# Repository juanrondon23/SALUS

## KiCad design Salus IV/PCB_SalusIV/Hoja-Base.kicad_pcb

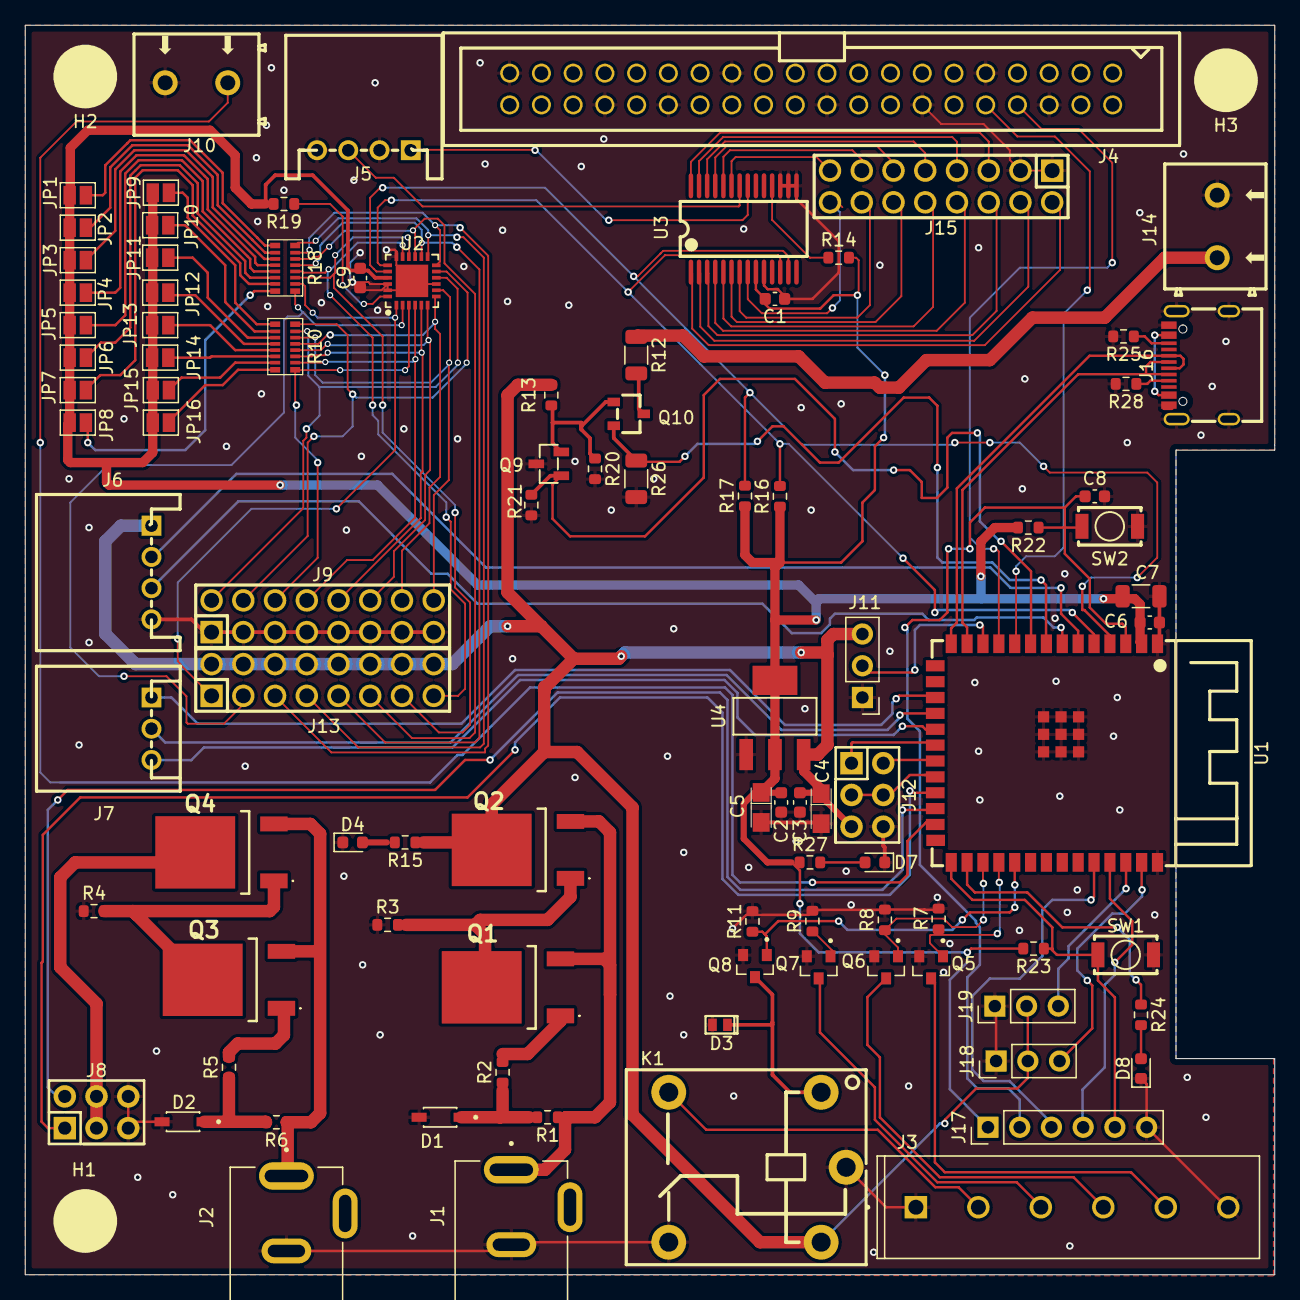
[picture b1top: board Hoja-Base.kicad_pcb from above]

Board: 2 copper layers, 100.0 x 100.0 mm, 98 parts (0 on the bottom side), 107 nets.

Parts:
C1, C2, C3, C6, C8, C9: 100nF; C_0603_1608Metric
C4, C5: 22uF; CASE-A_3216
C7: 22uF; C_1206_3216Metric
D1: BZT52C3V3; SOD3715X135N
D2: BZT52C5V1; SOD3715X135N
D3: TPTVS0971P; DFN1610-2L_L1.6-W1.0-P1.10-RD
D4: LED_Encendido; LED_0603_1608Metric
D7: LED_ESP32_RED; LED_0603_1608Metric
D8: LED_ESP32_YELLOW; LED_0603_1608Metric
H1, H2, H3: MountingHole; MountingHole_3.2mm_M3
J1, J2: DC-005-5A-2.0; XKB_DC-005-5A-2.0
J3: 282836-6; TE_282836-6
J4: IDC-TH_40P-P2.54_C9138
J5, J6: CONN-TH_S4B-XH-A-LF-SN
J7: CONN-TH_S3B-XH-A-LF-SN
J8, J12: HDR-TH_6P-P2.54-V-M-R2-C3-S2.54-1
J9, J13, J15: HDR-TH_16P-P2.54-V-M-R2-C8-S2.54
J10, J14: CONN-TH_2P-P5.00_CPC3703CTR
J11: RC; PinHeader_1x03_P2.54mm_Vertical
J16: USB-C-SMD_G-SWITCH_GT-USB-7010ASV
J17: Pruebas; PinHeader_1x06_P2.54mm_Vertical
J18: GPIO2-Libre; PinHeader_1x03_P2.54mm_Vertical
J19: GPIO1-Libre; PinHeader_1x03_P2.54mm_Vertical
JP1, JP2, JP3, JP4, JP5, JP6, JP7, JP8, JP9, JP10, JP11, JP12, JP13, JP14, JP15, JP16: Jumper_Soldado; SolderJumper-2_P1.3mm_Open_Pad1.0x1.5mm
K1: Relé-Arranque; RELAY-TH_SRD-XXVDC-XL-C
Q1, Q2, Q3, Q4: IRFR5305TRPBF
Q5, Q6, Q7, Q8: IRLML6344TRPBF; TRANS_IRLML6344TRPBF
Q9: SI2301CDS
Q10: RQ5P0
R1, R6, R13: 1K; R_0603_1608Metric
R2, R5, R7, R8, R9, R11, R20, R21: 47K; R_0603_1608Metric
R3, R4: 6.8K; R_0603_1608Metric
R10, R18: 4.7kΩ; RES-ARRAY-SMD_1606-16P-L4.0-W1.6-BL
R12: 47K; R_1206_3216Metric
R14, R22, R23: 10K; R_0603_1608Metric
R15: 390; R_0603_1608Metric
R16, R17, R19: 4.7K; R_0603_1608Metric
R24, R27: 180; R_0603_1608Metric
R25, R28: 5.1K; R_0603_1608Metric
R26: 1.5K; R_1206_3216Metric
SW1, SW2: Boton_Simple
U1: ESP32-S3-WROOM-1-N16; WIRELM-SMD_ESP32-S3-WROOM-1
U2: TCA; VQFN-24_L4.0-W4.0-P0.50-BL-EP2.5
U3: MCP; SSOP-28_L10.2-W5.3-P0.65-LS7.8-BL
U4: AMS; AMS1117

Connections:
7V: J8.3, J8.4, Q4.2 (D)
60V: J14.1, R12.1
+3.3V: C1.1, C2.1, C5.1, C6.1, C7.1, C9.1, J17.1, JP1.1 (A), JP2.1 (A), JP3.1 (A), JP4.1 (A), JP5.1 (A), JP6.1 (A), JP7.1 (A), JP8.1 (A), JP9.1 (A), JP10.1 (A), JP11.1 (A), JP12.1 (A), JP13.1 (A), JP14.1 (A), JP15.1 (A), JP16.1 (A), R14.2, R16.1, R17.1, R19.2, R22.2, R23.2, R27.1, U1.2 (3V3), U2.21 (VCC), U3.9 (VDD), U4.2 (VOUT), U4.4 (VOUT)
+5V: C3.1, C4.1, J6.1, J11.3, J12.5, J13.2, J13.4, J13.6, J13.8, J13.10, J13.12, J13.14, J13.16, J18.2, J19.2, K1.4, Q2.2 (D), R13.1, R15.1, U4.3 (VIN)
ACELERADOR: J10.1, U1.25 (IO48)
ADC_ES: Q10.2 (S), R26.1, U1.8 (IO15)
Arranque: Q8.1, R11.1, U1.31 (IO38)
BOOT: J17.5, R23.1, SW1.1, U1.27 (IO0)
CARRERA 1: J5.1, U3.21 (GPA0)
CARRERA 2: J5.3, U3.22 (GPA1)
Cambio: Q6.1, R8.1, U1.29 (IO36)
Control_Bat: Q9.1 (G), R21.1, U1.9 (IO16)
ENABLE: J12.3, J12.4, U1.22 (IO14)
Expansor 3: J15.15, U3.23 (GPA2)
Expansor 4: J15.13, U3.24 (GPA3)
Expansor 5: J15.11, U3.25 (GPA4)
Expansor 6: J15.9, U3.26 (GPA5)
Expansor 7: J15.7, U3.27 (GPA6)
Expansor 8: J15.5, U3.28 (GPA7)
Expansor 9: J15.16, U3.8 (GPB7)
Expansor 10: J15.14, U3.7 (GPB6)
Expansor 11: J15.12, U3.6 (GPB5)
Expansor 12: J15.10, U3.5 (GPB4)
Expansor 13: J15.8, U3.4 (GPB3)
Expansor 14: J15.6, U3.3 (GPB2)
Expansor 15: J15.4, U3.2 (GPB1)
Expansor 16: J15.2, U3.1 (GPB0)
GND: C1.2, C2.2, C3.2, C4.2, C5.2, C6.2, C7.2, C8.2, C9.2, D1.2 (A), D2.2 (A), D3.2 (A2), D4.1 (K), D7.1 (K), D8.1 (K), J1.2, J2.2, J3.1, J3.6, J4.6, J4.9, J4.14, J4.20, J4.25, J4.30, J4.34, J4.39, J5.2, J5.4, J6.4, J8.5, J8.6, J9.1, J9.3, J9.5, J9.7, J9.9, J9.11, J9.13, J9.15, J10.2, J11.1, J12.6, J14.2, J15.1, J15.3, J16.1 (SHELL), J16.2 (SHELL), J16.3 (SHELL), J16.4 (SHELL), J16.A1B12 (GND), J16.B1A12 (GND), J17.6, J18.1, J19.1, K1.3, K1.5, Q5.2, Q6.2, Q7.2, Q8.2, Q9.3 (D), R3.1, R4.1, R7.2, R8.2, R9.2, R11.2, R20.2, R21.2, R25.2, R26.2, R28.2, SW1.2, SW2.2, U1.1 (GND), U1.40 (GND), U1.41 (GND), U2.9 (GND), U2.18 (A2), U2.22 (A0), U2.23 (A1), U2.25 (EP), U3.10 (VSS), U3.15 (A0), U3.16 (A1), U3.17 (A2), U4.1 (GND)
GPIO1: J18.3, U1.39 (IO1)
GPIO2: J19.3, U1.38 (IO2)
HALL-1: J7.1, U1.17 (IO9)
HALL-2: J7.2, U1.18 (IO10)
HALL-3: J7.3, U1.19 (IO11)
LED-Gpio: R24.1, U1.28 (IO35)
LPWM: J12.2, U1.21 (IO13)
Luces: Q7.1, R9.1
unnamed: D1.1 (K), R1.2, R2.1
unnamed: D2.1 (K), R5.1, R6.2
unnamed: D3.1 (A1), K1.1, Q8.3
unnamed: D4.2 (A), R15.2
unnamed: D7.2 (A), R27.2
unnamed: D8.2 (A), R24.2
unnamed: J3.2, K1.2
unnamed: J3.3, Q7.3
unnamed: J3.4, Q6.3
unnamed: J3.5, Q5.3
unnamed: J16.A5 (CC1), R28.1
unnamed: J16.B5 (CC2), R25.1
unnamed: J17.3, U1.36 (RXD0)
unnamed: J17.4, U1.37 (TXD0)
unnamed: JP1.2 (B), R18.1
unnamed: JP2.2 (B), R18.2
unnamed: JP3.2 (B), R18.3
unnamed: JP4.2 (B), R18.4
unnamed: JP5.2 (B), R18.5
unnamed: JP6.2 (B), R18.6
unnamed: JP7.2 (B), R18.7
unnamed: JP8.2 (B), R18.8
unnamed: JP9.2 (B), R10.1
unnamed: JP10.2 (B), R10.2
unnamed: JP11.2 (B), R10.3
unnamed: JP12.2 (B), R10.4
unnamed: JP13.2 (B), R10.5
unnamed: JP14.2 (B), R10.6
unnamed: JP15.2 (B), R10.7
unnamed: JP16.2 (B), R10.8
unnamed: Q1.2 (D), Q2.1 (G), R3.2
unnamed: Q1.1 (G), R2.2
unnamed: J1.1, Q1.3 (S), Q2.3 (S), R1.1
unnamed: Q3.2 (D), Q4.1 (G), R4.2
unnamed: Q3.1 (G), R5.2
unnamed: J2.1, Q3.3 (S), Q4.3 (S), R6.1
unnamed: Q10.3 (D), R12.2
unnamed: Q9.2 (S), Q10.1 (G), R13.2, R20.1
unnamed: R14.1, U3.18 (RESET#)
PPM: J11.2, U1.12 (IO8)
RESET: C8.1, J17.2, R22.1, SW2.1, U1.3 (EN)
RPWM: J12.1, U1.20 (IO12)
RST: R19.1, U2.24 (RESET#)
RX1: J4.8, U1.11 (IO18)
Reversa: Q5.1, R7.1, U1.30 (IO37)
SC0: J13.3, R18.9, U2.2 (SC0)
SC1: J9.8, R10.10, U2.4 (SC1)
SC2: J9.12, R10.12, U2.6 (SC2)
SC3: J9.16, R10.14, U2.8 (SC3)
SC4: J9.4, R10.16, U2.11 (SC4)
SC5: J13.7, R18.16, U2.13 (SC5)
SC6: J13.11, R18.14, U2.15 (SC6)
SC7: J13.15, R18.12, U2.17 (SC7)
SCL-Expansores: R16.2, U1.5 (IO5), U2.19 (SCL), U3.12 (SCK)
SCL-Giro: J6.3, U1.7 (IO7)
SD0: J13.1, R18.10, U2.1 (SD0)
SD1: J9.6, R10.9, U2.3 (SD1)
SD2: J9.10, R10.11, U2.5 (SD2)
SD3: J9.14, R10.13, U2.7 (SD3)
SD4: J9.2, R10.15, U2.10 (SD4)
SD5: J13.5, R18.15, U2.12 (SD5)
SD6: J13.9, R18.13, U2.14 (SD6)
SD7: J13.13, R18.11, U2.16 (SD7)
SDA-Expansores: R17.2, U1.4 (IO4), U2.20 (SDA), U3.13 (SDA)
SDA-Giro: J6.2, U1.6 (IO6)
Servo1: J8.2, U1.24 (IO47)
Servo2: J8.1, U1.23 (IO21)
TX1: J4.10, U1.10 (IO17)
USB+: J16.A6 (DP1), J16.B6 (DP2), U1.14 (IO20)
USB-: J16.A7 (DN1), J16.B7 (DN2), U1.13 (IO19)
VBUS: J16.A4B9 (VBUS), J16.B4A9 (VBUS)

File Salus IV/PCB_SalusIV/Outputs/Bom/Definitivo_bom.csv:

Designator,Footprint,Quantity,Value,LCSC Part #
"C1, C2, C3, C6, C8, C9",0603,6,100nF,C1590
"C4, C5",CASE-A_3216,2,22uF,C7182
C7,1206,1,22uF,C5672
D1,SOD3715X135N,1,BZT52C3V3,C151564
D2,SOD3715X135N,1,BZT52C5V1,C151588
D3,DFN1610-2L_L1.6-W1.0-P1.10-RD,1,TPTVS0971P,C2923378
D4,0603,1,LED_Encendido,C2297
D7,0603,1,LED_ESP32_RED, C2286 
D8,0603,1,LED_ESP32_YELLOW,C2296
"J1, J2",XKB_DC-005-5A-2.0,2,DC-005-5A-2.0,C381116
"J10, J14",CONN-TH_2P-P5.00_CPC3703CTR,2,~,C3703
J11,PinHeader_1x03_P2.54mm_Vertical,1,RC,C52016391
"J12, J8",HDR-TH_6P-P2.54-V-M-R2-C3-S2.54-1,2,~,C65114
"J13, J15, J9",HDR-TH_16P-P2.54-V-M-R2-C8-S2.54,3,~, C68234
J16,USB-C-SMD_G-SWITCH_GT-USB-7010ASV,1,~,C2988369
J3,TE_282836-6,1,282836-6,C192781
J4,IDC-TH_40P-P2.54_C9138,1,~,C9138
"J5, J6",CONN-TH_S4B-XH-A-LF-SN,2,~,C157925
J7,CONN-TH_S3B-XH-A-LF-SN,1,~,C157928
JP11,SolderJumper-2_P1.3mm_Open_Pad1.0x1.5mm,1,Jumper_Soldado,
K1,RELAY-TH_SRD-XXVDC-XL-C,1,Relé-Arranque,C35449
"Q1, Q2, Q3, Q4",IRFR5305TRPBF,4,IRFR5305TRPBF,C2624
Q10,RQ5P0,1,~,C962659
"Q5, Q6, Q7, Q8",TRANS_IRLML6344TRPBF,4,IRLML6344TRPBF,C22367220
Q9,SI2301CDS,1,~,C5197335
"R1, R13, R6",0603,3,1K,C14676
"R10, R18",RES-ARRAY-SMD_1606-16P-L4.0-W1.6-BL,2,4.7kΩ,C706486
"R11, R2, R20, R21, R5, R7, R8, R9",0603,8,47K,C105579
R12,1206,1,47K,C136469
"R14, R22, R23",0603,3,10K,C98220
R15,0603,1,390,C114620
"R16, R17, R19",0603,3,4.7K,C99782
"R24, R27",0603,2,180,C4316945
"R25, R28",0603,2,5.1K,C14677
R26,1206,1,1.5K,C114929
"R3, R4",0603,2,6.8K,C114632
"SW1, SW2",Boton_Simple,2,~,C36936655
U1,WIRELM-SMD_ESP32-S3-WROOM-1,1,ESP32-S3-WROOM-1-N16,C2913199
U2,VQFN-24_L4.0-W4.0-P0.50-BL-EP2.5,1,TCA,C555456
U3,SSOP-28_L10.2-W5.3-P0.65-LS7.8-BL,1,MCP,C558584
U4,AMS1117,1,AMS,C6186

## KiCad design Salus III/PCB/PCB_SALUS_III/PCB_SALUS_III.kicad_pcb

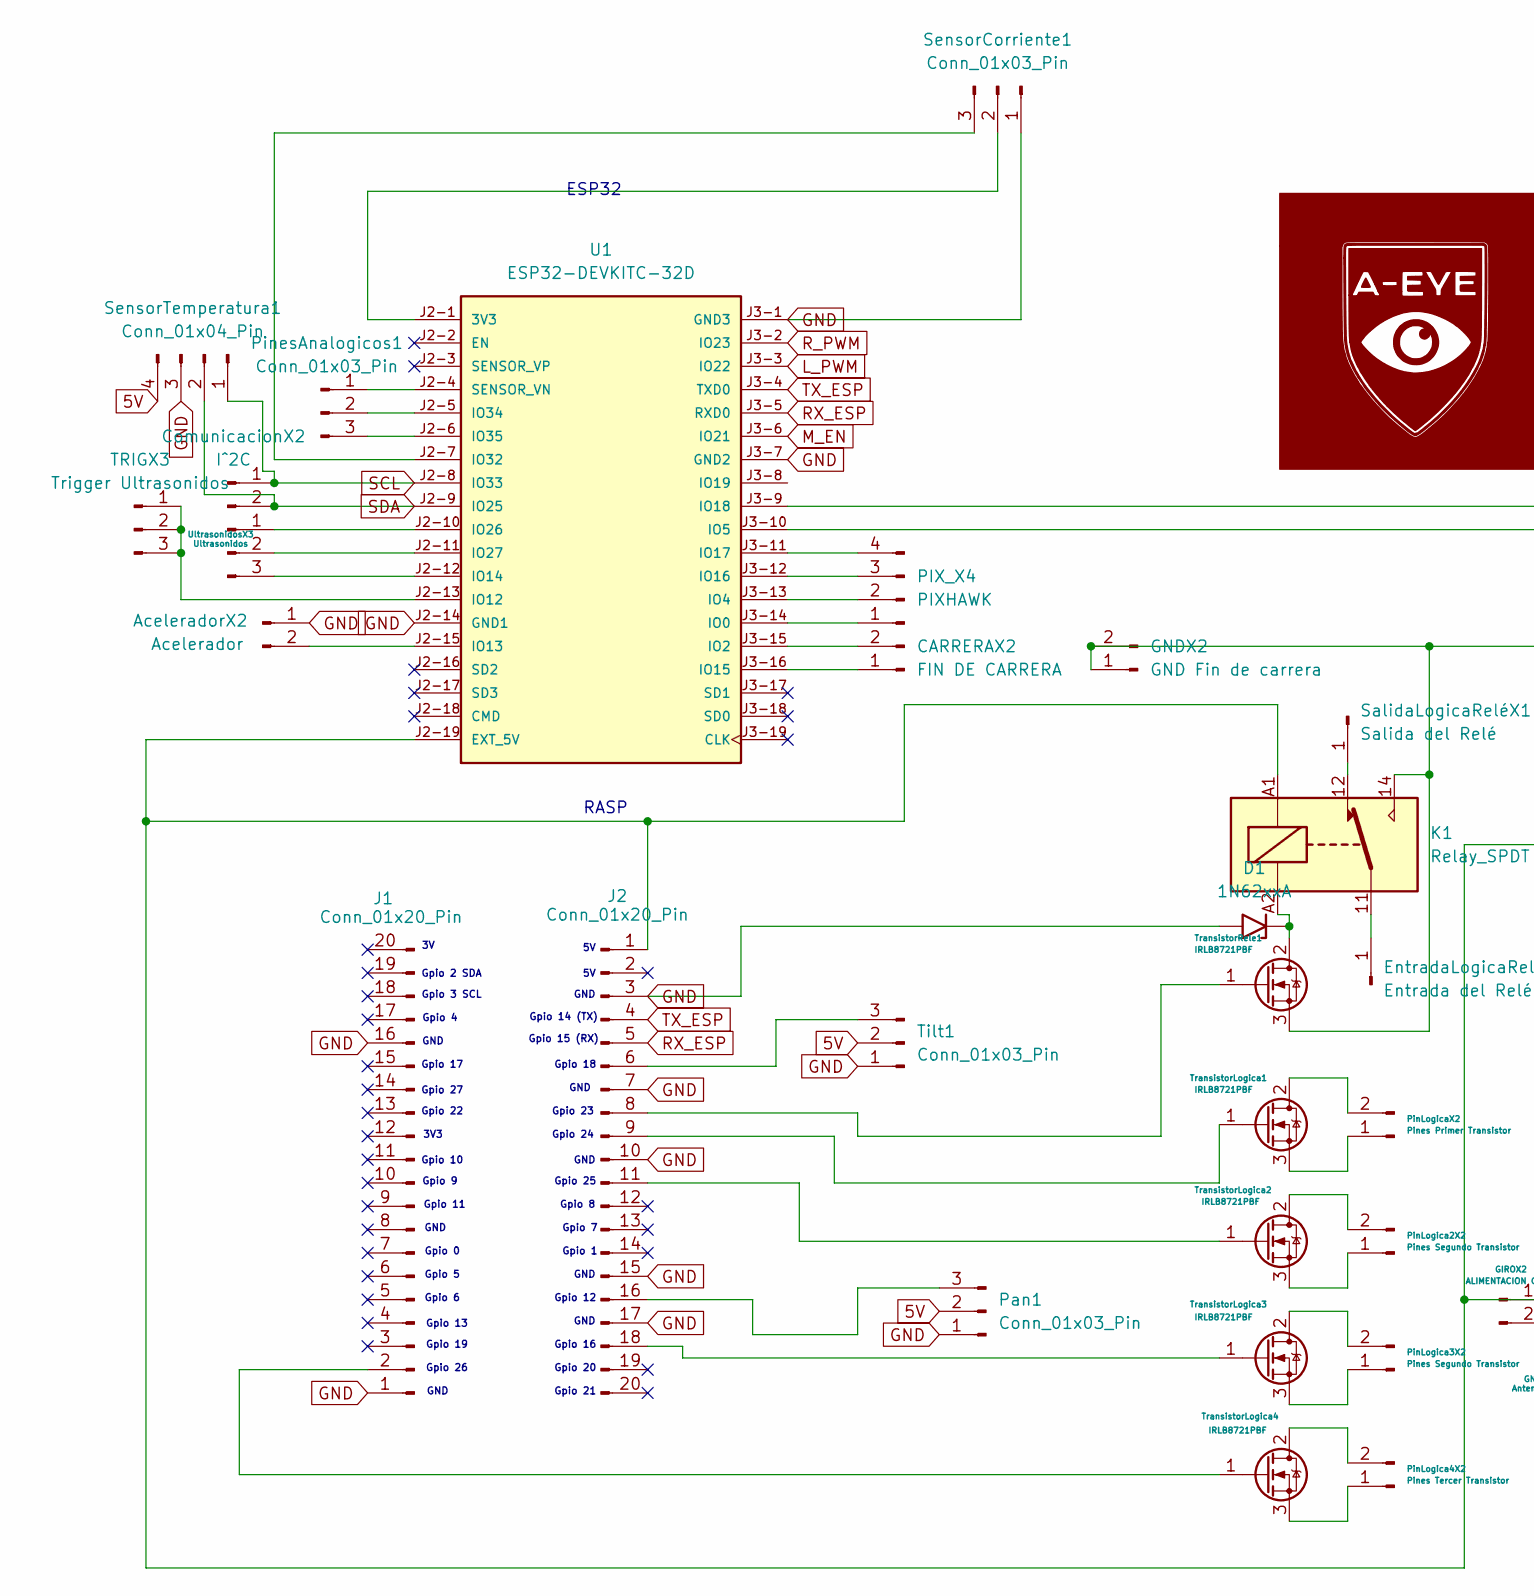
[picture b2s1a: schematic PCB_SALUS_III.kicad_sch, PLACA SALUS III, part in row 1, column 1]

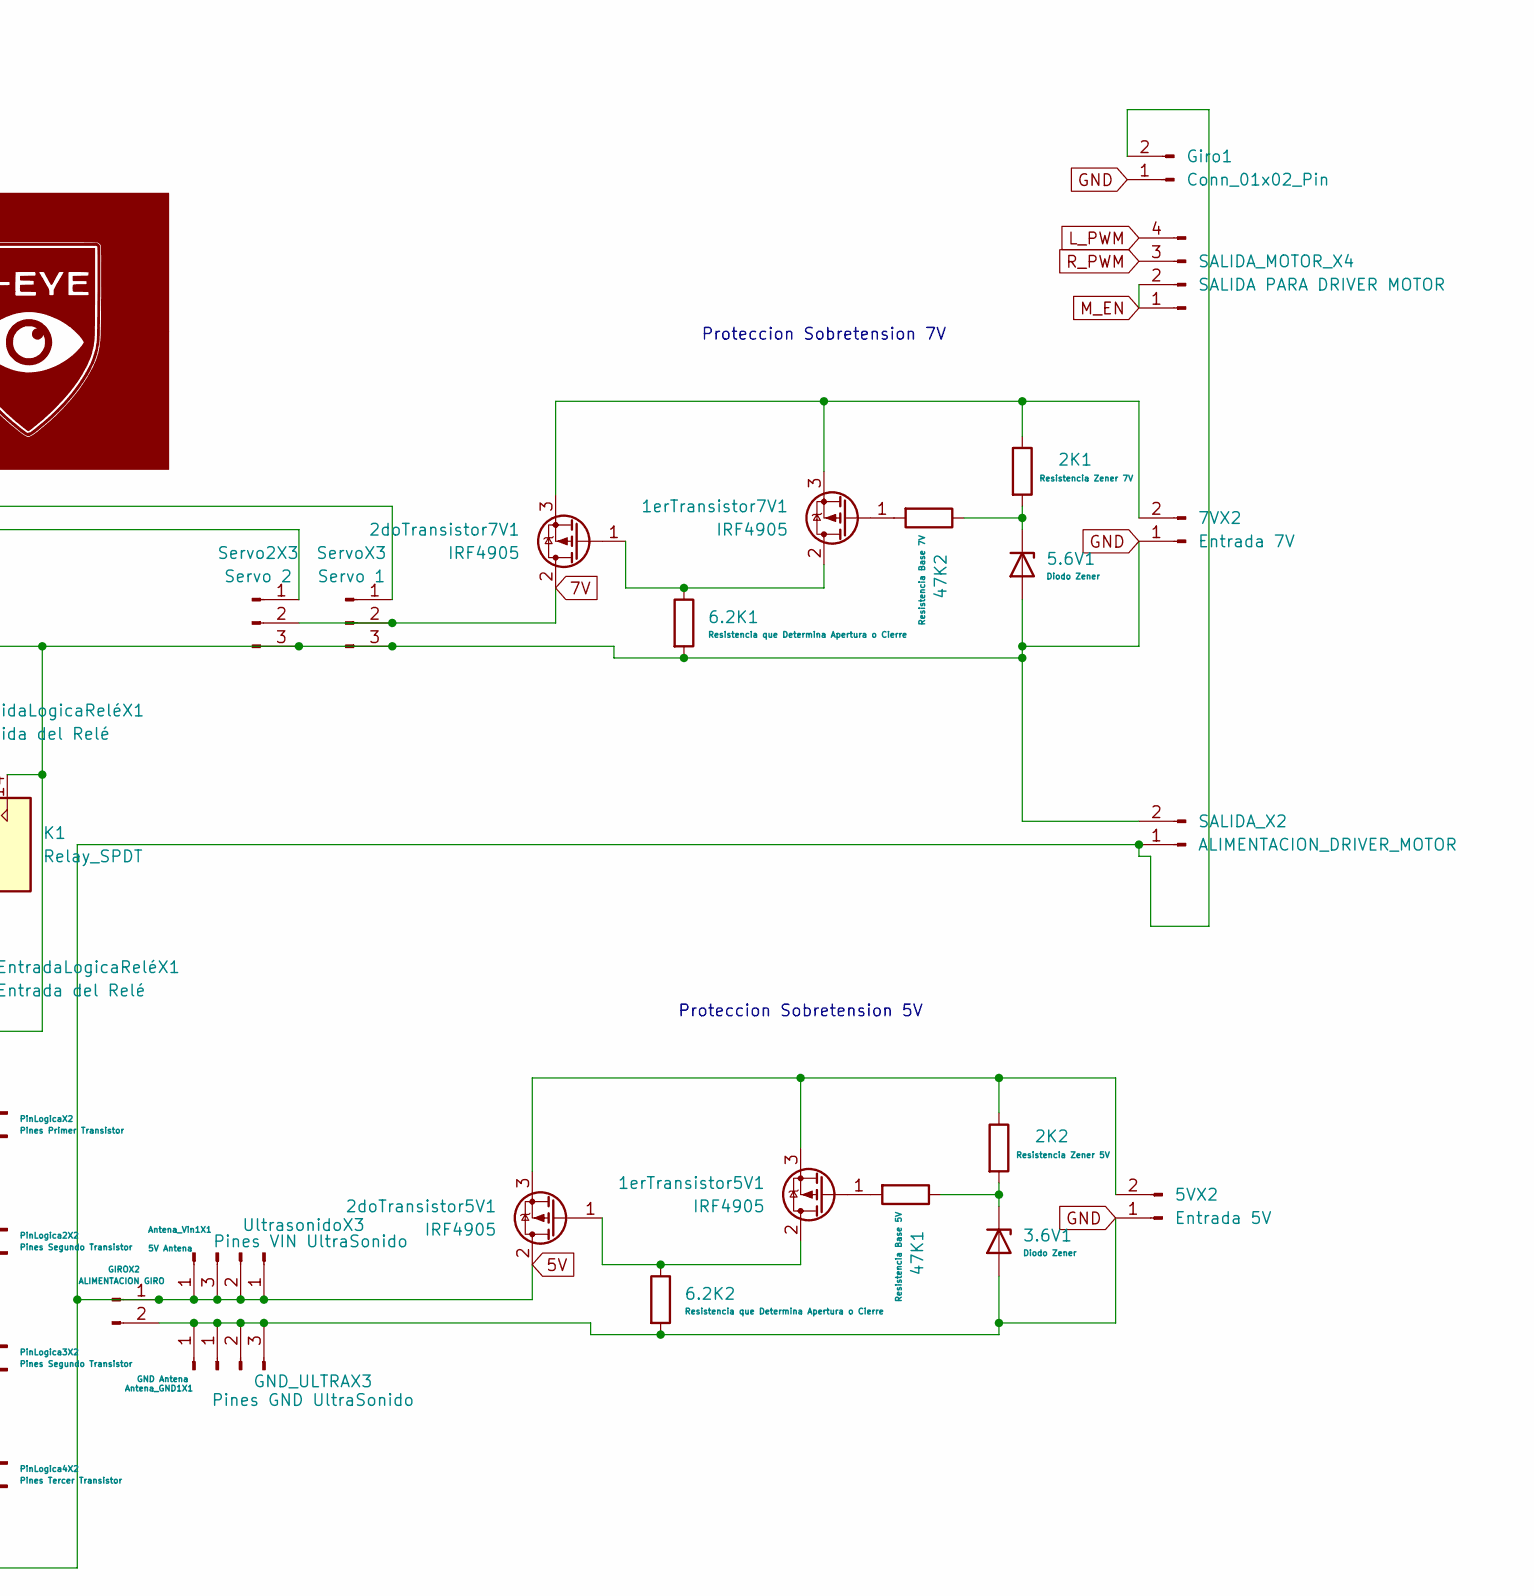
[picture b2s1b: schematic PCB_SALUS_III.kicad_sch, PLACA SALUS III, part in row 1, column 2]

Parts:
1erTransistor5V1, 1erTransistor7V1, 2doTransistor5V1, 2doTransistor7V1: IRF4905; TO-220-3_Vertical
2K1: Resistencia Zener 7V; R_Axial_DIN0207_L6.3mm_D2.5mm_P10.16mm_Horizontal
2K2: Resistencia Zener 5V; R_Axial_DIN0207_L6.3mm_D2.5mm_P10.16mm_Horizontal
3.6V1, 5.6V1: Diodo Zener; D_DO-41_SOD81_P12.70mm_Horizontal
5VX2: Entrada 5V; PinHeader_1x02_P2.54mm_Vertical
6.2K1, 6.2K2: Resistencia que Determina Apertura o Cierre; R_Axial_DIN0207_L6.3mm_D2.5mm_P10.16mm_Horizontal
7VX2: Entrada 7V; PinHeader_1x02_P2.54mm_Vertical
47K1: Resistencia Base 5V; R_Axial_DIN0207_L6.3mm_D2.5mm_P10.16mm_Horizontal
47K2: Resistencia Base 7V; R_Axial_DIN0207_L6.3mm_D2.5mm_P10.16mm_Horizontal
AceleradorX2: Acelerador; PinHeader_1x02_P2.54mm_Vertical
Antena_GND1X1: GND Antena; PinHeader_1x01_P2.54mm_Vertical
Antena_Vin1X1: 5V Antena; PinHeader_1x01_P2.54mm_Vertical
CARRERAX2: FIN DE CARRERA; PinHeader_1x02_P2.54mm_Vertical
ComunicacionX2: I^2C; PinHeader_1x02_P2.54mm_Vertical
D1: 1N62xxA; D_DO-201AE_P15.24mm_Horizontal
EntradaLogicaReléX1: Entrada del Relé; PinHeader_1x01_P2.54mm_Vertical
GIROX2: ALIMENTACION GIRO; PinHeader_1x02_P2.54mm_Vertical
GNDX2: GND Fin de carrera; PinHeader_1x02_P2.54mm_Vertical
GND_ULTRAX3: Pines GND UltraSonido; PinHeader_1x03_P2.54mm_Vertical
Giro1: Conn_01x02_Pin; PinHeader_1x02_P2.54mm_Vertical
J1, J2: Conn_01x20_Pin; PinHeader_1x20_P2.54mm_Vertical
K1: Relay_SPDT; Relay_SPDT_Finder_36.11
PIX_X4: PIXHAWK; PinSocket_1x04_P2.54mm_Vertical
Pan1: Conn_01x03_Pin; PinHeader_1x03_P2.54mm_Vertical
PinLogica2X2, PinLogica3X2: Pines Segundo Transistor; PinHeader_1x02_P2.54mm_Vertical
PinLogica4X2: Pines Tercer Transistor; PinHeader_1x02_P2.54mm_Vertical
PinLogicaX2: Pines Primer Transistor; PinHeader_1x02_P2.54mm_Vertical
PinesAnalogicos1: Conn_01x03_Pin; PinHeader_1x03_P2.54mm_Vertical
SALIDA_MOTOR_X4: SALIDA PARA DRIVER MOTOR; PinHeader_1x04_P2.54mm_Vertical
SALIDA_X2: ALIMENTACION_DRIVER_MOTOR; PinHeader_1x02_P2.54mm_Vertical
SalidaLogicaReléX1: Salida del Relé; PinHeader_1x01_P2.54mm_Vertical
SensorCorriente1: Conn_01x03_Pin; PinHeader_1x03_P2.54mm_Vertical
SensorTemperatura1: Conn_01x04_Pin; PinHeader_1x04_P2.54mm_Vertical
Servo2X3: Servo 2; PinHeader_1x03_P2.54mm_Vertical
ServoX3: Servo 1; PinHeader_1x03_P2.54mm_Vertical
TRIGX3: Trigger Ultrasonidos; PinHeader_1x03_P2.54mm_Vertical
Tilt1: Conn_01x03_Pin; PinHeader_1x03_P2.54mm_Vertical
TransistorLogica1, TransistorLogica2, TransistorLogica3, TransistorLogica4: IRLB8721PBF; TO-220-3_Vertical
TransistorRele1: IRLB8721PBF; TO-220-3_Vertical
U1: ESP32-DEVKITC-32D; MODULE_ESP32-DEVKITC-32D; PARTREV V4
UltrasonidoX3: Pines VIN UltraSonido; PinHeader_1x03_P2.54mm_Vertical
UltrasonidosX3: Ultrasonidos; PinHeader_1x03_P2.54mm_Vertical

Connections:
5V: 2doTransistor5V1.2 (D), Antena_Vin1X1.1, GIROX2.1, Giro1.2, J2.1, K1.A1, Pan1.2, SALIDA_X2.1, SensorTemperatura1.4, Tilt1.2, U1.J2-19 (EXT_5V), UltrasonidoX3.1, UltrasonidoX3.2, UltrasonidoX3.3
7V: 2doTransistor7V1.2 (D), Servo2X3.2, ServoX3.2
GND: 3.6V1.2 (A), 5.6V1.2 (A), 5VX2.1, 6.2K1.2, 6.2K2.2, 7VX2.1, AceleradorX2.1, Antena_GND1X1.1, D1.2 (A2), GIROX2.2, GNDX2.1, GNDX2.2, GND_ULTRAX3.1, GND_ULTRAX3.2, GND_ULTRAX3.3, Giro1.1, J1.1, J1.16, J2.3, J2.7, J2.10, J2.15, J2.17, K1.14, Pan1.1, SALIDA_X2.2, SensorCorriente1.1, SensorTemperatura1.3, Servo2X3.3, ServoX3.3, Tilt1.1, TransistorRele1.3 (S), U1.J2-14 (GND1), U1.J3-1 (GND3), U1.J3-7 (GND2)
L_PWM: SALIDA_MOTOR_X4.4, U1.J3-3 (IO22)
M_EN: SALIDA_MOTOR_X4.1, SALIDA_MOTOR_X4.2, U1.J3-6 (IO21)
unnamed: 1erTransistor5V1.2 (D), 2doTransistor5V1.1 (G), 6.2K2.1
unnamed: 1erTransistor5V1.1 (G), 47K1.2
unnamed: 1erTransistor5V1.3 (S), 2K2.1, 2doTransistor5V1.3 (S), 5VX2.2
unnamed: 1erTransistor7V1.2 (D), 2doTransistor7V1.1 (G), 6.2K1.1
unnamed: 1erTransistor7V1.1 (G), 47K2.2
unnamed: 1erTransistor7V1.3 (S), 2K1.1, 2doTransistor7V1.3 (S), 7VX2.2
unnamed: 2K2.2, 3.6V1.1 (K), 47K1.1
unnamed: 2K1.2, 5.6V1.1 (K), 47K2.1
unnamed: AceleradorX2.2, U1.J2-15 (IO13)
unnamed: CARRERAX2.1, U1.J3-16 (IO15)
unnamed: CARRERAX2.2, U1.J3-15 (IO2)
unnamed: D1.1 (A1), K1.A2, TransistorRele1.2 (D)
unnamed: EntradaLogicaReléX1.1, K1.11
unnamed: J1.2, TransistorLogica4.1 (G)
unnamed: J2.6, Tilt1.3
unnamed: J2.8, TransistorRele1.1 (G)
unnamed: J2.9, TransistorLogica1.1 (G)
unnamed: J2.11, TransistorLogica2.1 (G)
unnamed: J2.16, Pan1.3
unnamed: J2.18, TransistorLogica3.1 (G)
unnamed: PIX_X4.1, U1.J3-14 (IO0)
unnamed: PIX_X4.2, U1.J3-13 (IO4)
unnamed: PIX_X4.3, U1.J3-12 (IO16)
unnamed: PIX_X4.4, U1.J3-11 (IO17)
unnamed: PinLogica2X2.1, TransistorLogica2.3 (S)
unnamed: PinLogica2X2.2, TransistorLogica2.2 (D)
unnamed: PinLogica3X2.1, TransistorLogica3.3 (S)
unnamed: PinLogica3X2.2, TransistorLogica3.2 (D)
unnamed: PinLogica4X2.1, TransistorLogica4.3 (S)
unnamed: PinLogica4X2.2, TransistorLogica4.2 (D)
unnamed: PinLogicaX2.1, TransistorLogica1.3 (S)
unnamed: PinLogicaX2.2, TransistorLogica1.2 (D)
unnamed: PinesAnalogicos1.1, U1.J2-4 (SENSOR_VN)
unnamed: PinesAnalogicos1.2, U1.J2-5 (IO34)
unnamed: PinesAnalogicos1.3, U1.J2-6 (IO35)
unnamed: K1.12, SalidaLogicaReléX1.1
unnamed: SensorCorriente1.2, U1.J2-1 (3V3)
unnamed: SensorCorriente1.3, U1.J2-7 (IO32)
unnamed: Servo2X3.1, U1.J3-10 (IO5)
unnamed: ServoX3.1, U1.J3-9 (IO18)
unnamed: TRIGX3.1, TRIGX3.2, TRIGX3.3, U1.J2-13 (IO12)
unnamed: U1.J2-12 (IO14), UltrasonidosX3.3
unnamed: U1.J2-10 (IO26), UltrasonidosX3.1
unnamed: U1.J2-11 (IO27), UltrasonidosX3.2
RX_ESP: J2.5, U1.J3-5 (RXD0)
R_PWM: SALIDA_MOTOR_X4.3, U1.J3-2 (IO23)
SCL: ComunicacionX2.1, SensorTemperatura1.1, U1.J2-8 (IO33)
SDA: ComunicacionX2.2, SensorTemperatura1.2, U1.J2-9 (IO25)
TX_ESP: J2.4, U1.J3-4 (TXD0)

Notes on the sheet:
Gpio 10
Gpio 8
GND
Gpio 18
Gpio 24
Gpio 14 (TX)
Gpio 12
Proteccion Sobretension 7V
3V3
Gpio 11
Proteccion Sobretension 5V
Gpio 3 SCL
Gpio 27
Gpio 0
Gpio 2 SDA
Gpio 17
RASP
Gpio 21
Gpio 23
Gpio 25
Gpio 9
Gpio 6
Gpio 7
Gpio 4
Gpio 22
Gpio 13
Gpio 16
ESP32
Gpio 20
Gpio 5
Gpio 19
Gpio 26
Gpio 15 (RX)
Gpio 1

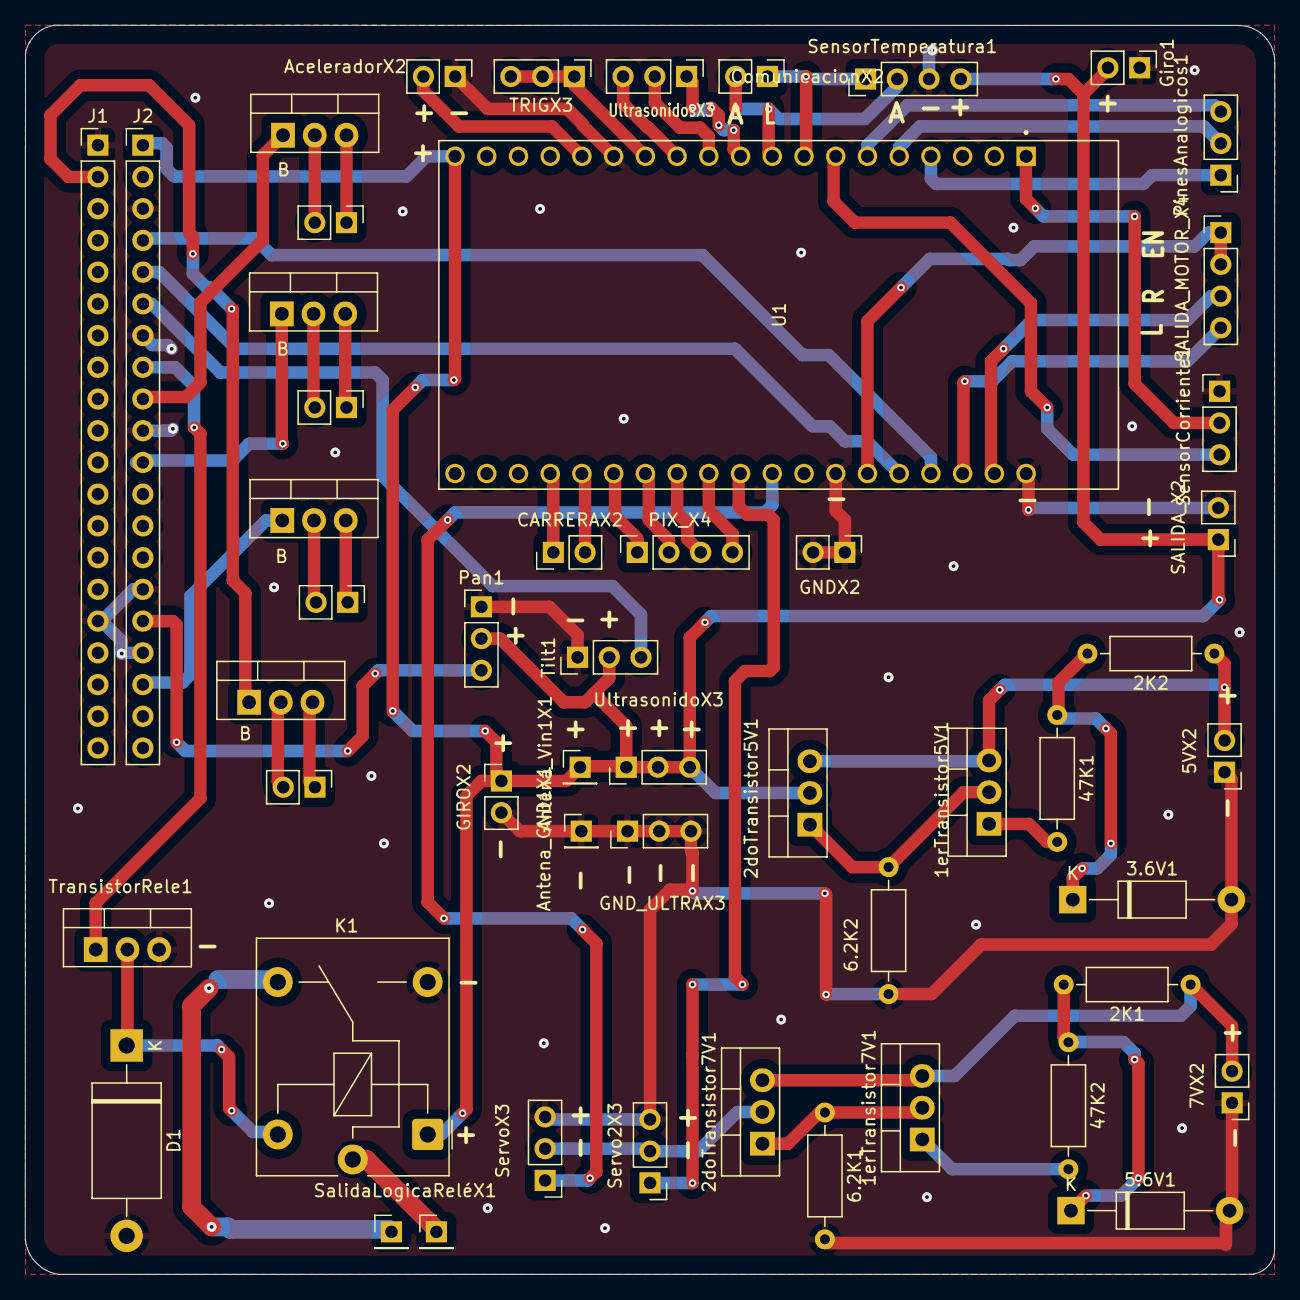
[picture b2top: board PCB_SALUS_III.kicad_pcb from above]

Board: 2 copper layers, 100.0 x 100.0 mm, 52 parts (0 on the bottom side), 54 nets.

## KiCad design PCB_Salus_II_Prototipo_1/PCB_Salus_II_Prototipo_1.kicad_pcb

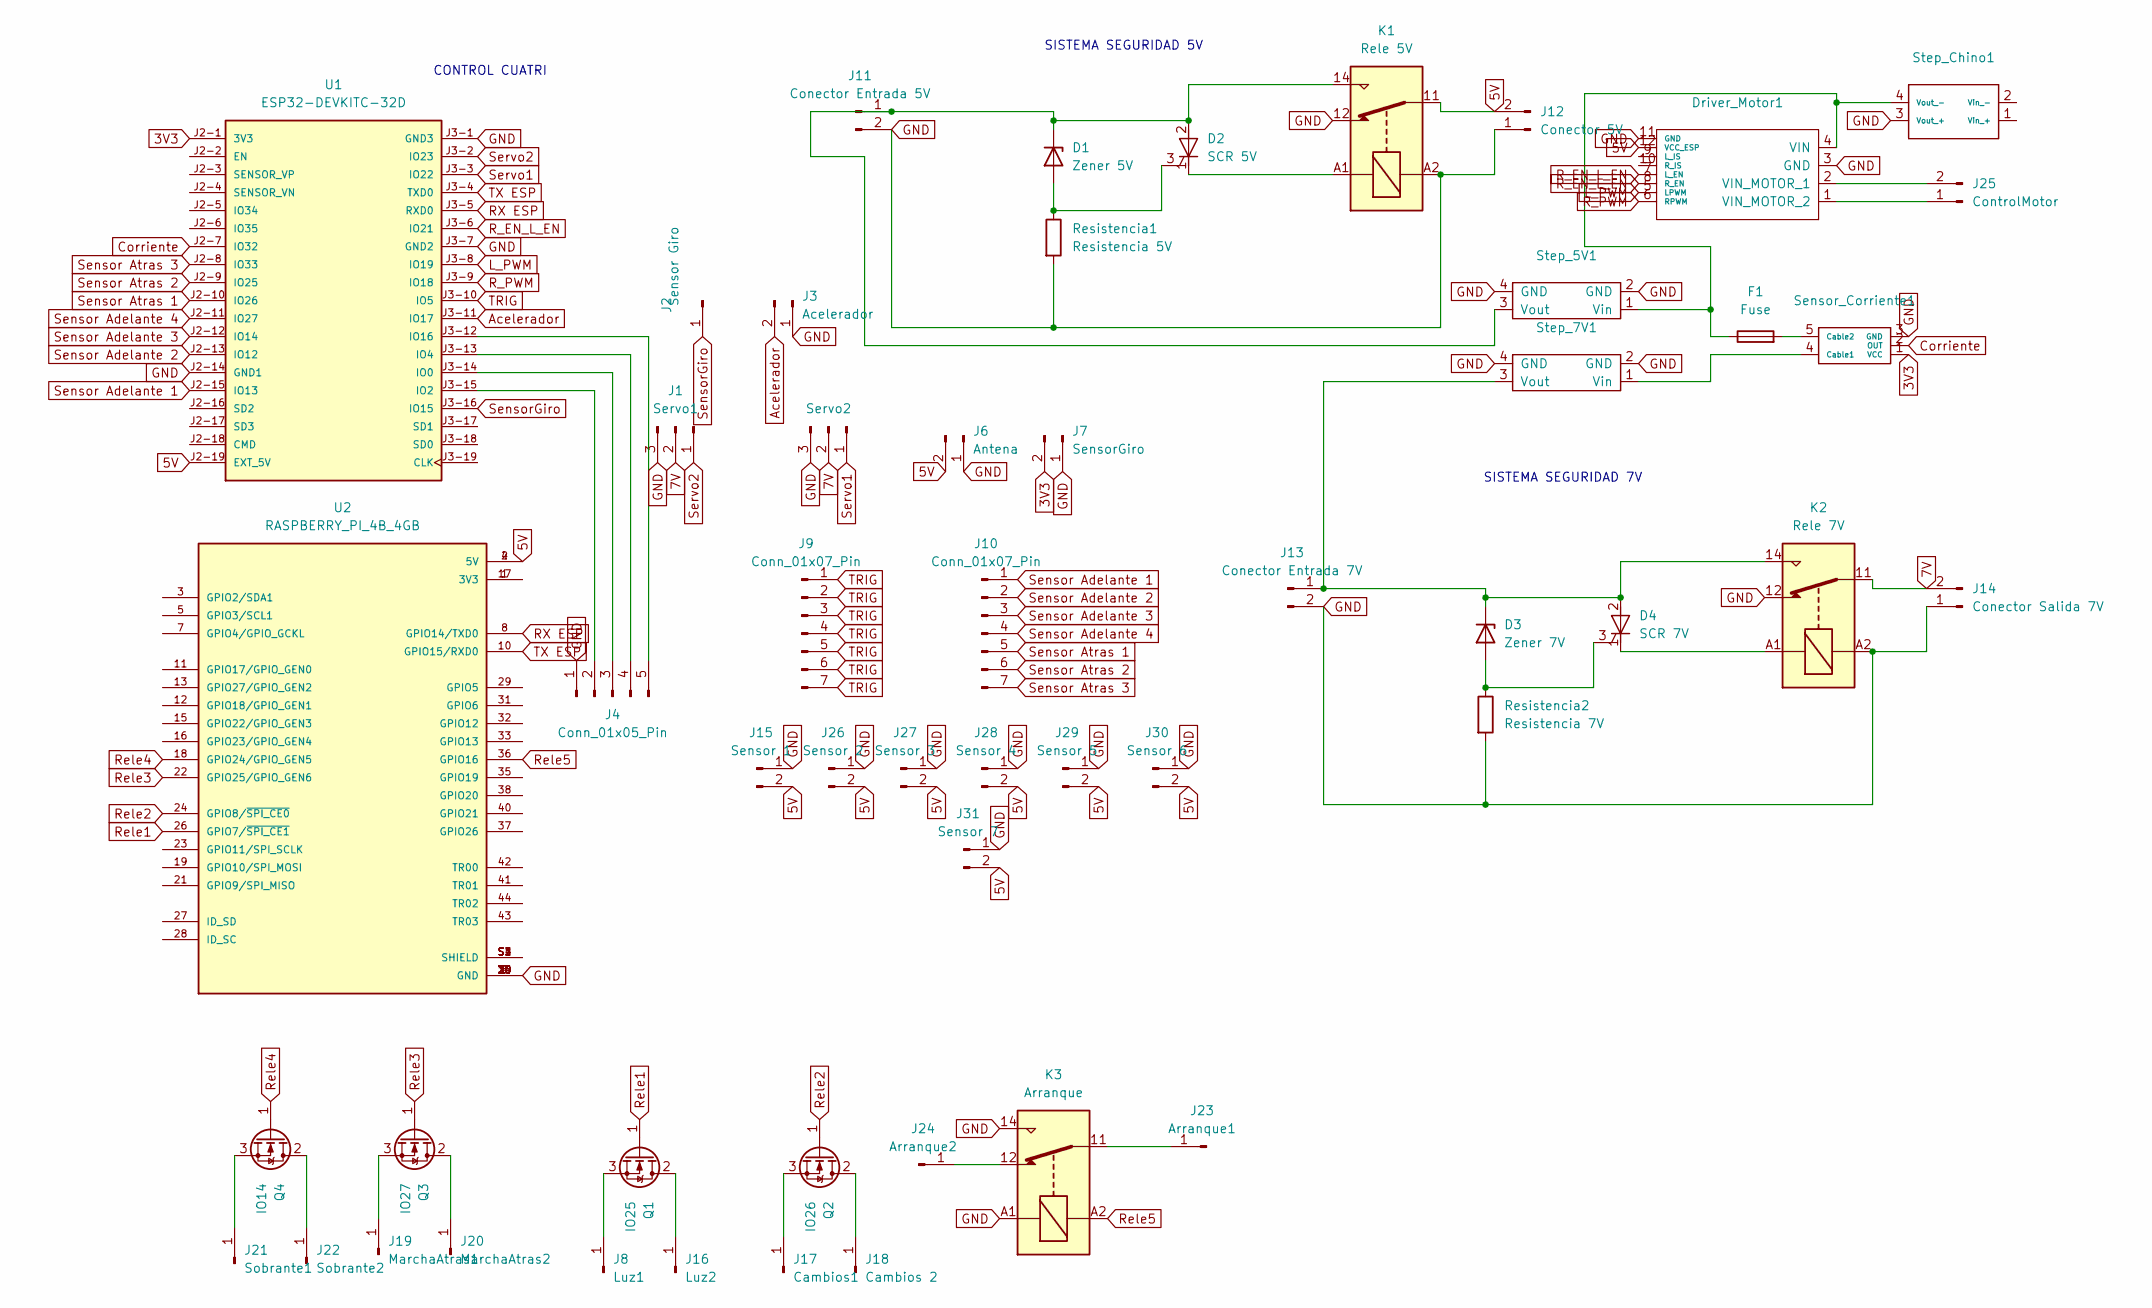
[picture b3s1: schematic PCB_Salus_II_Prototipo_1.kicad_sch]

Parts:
D1: Zener 5V; D_SOD-123
D2: SCR 5V; TO-220-3_Vertical
D3: Zener 7V; D_SOD-123
D4: SCR 7V; TO-220-3_Vertical
Driver_Motor1: Driver_Motor
F1: Fuse; Fuseholder_Clip-5x20mm_Eaton_1A5601-01_Inline_P20.80x6.76mm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
J1: Servo1; PinHeader_1x03_P2.54mm_Vertical
J2: Sensor Giro; PinHeader_1x01_P2.54mm_Vertical
J3: Acelerador; PinHeader_1x02_P2.54mm_Vertical
J4: Conn_01x05_Pin; PinHeader_1x05_P2.54mm_Vertical
J5: Servo2; PinHeader_1x03_P2.54mm_Vertical
J6: Antena; PinHeader_1x02_P2.54mm_Vertical
J7: SensorGiro; PinHeader_1x02_P2.54mm_Vertical
J8: Luz1; PinHeader_1x01_P2.54mm_Vertical
J9, J10: Conn_01x07_Pin; PinHeader_1x07_P2.54mm_Vertical
J11: Conector Entrada 5V; PinHeader_1x02_P2.54mm_Vertical
J12: Conector 5V; PinHeader_1x02_P2.54mm_Vertical
J13: Conector Entrada 7V; PinHeader_1x02_P2.54mm_Vertical
J14: Conector Salida 7V; PinHeader_1x02_P2.54mm_Vertical
J15: Sensor 1; PinHeader_1x02_P2.54mm_Vertical
J16: Luz2; PinHeader_1x01_P2.54mm_Vertical
J17: Cambios1; PinHeader_1x01_P2.54mm_Vertical
J18: Cambios 2; PinHeader_1x01_P2.54mm_Vertical
J19: MarchaAtras1; PinHeader_1x01_P2.54mm_Vertical
J20: MarchaAtras2; PinHeader_1x01_P2.54mm_Vertical
J21: Sobrante1; PinHeader_1x01_P2.54mm_Vertical
J22: Sobrante2; PinHeader_1x01_P2.54mm_Vertical
J23: Arranque1; PinHeader_1x01_P2.54mm_Vertical
J24: Arranque2; PinHeader_1x01_P2.54mm_Vertical
J25: ControlMotor; PinHeader_1x02_P2.54mm_Vertical
J26: Sensor 2; PinHeader_1x02_P2.54mm_Vertical
J27: Sensor 3; PinHeader_1x02_P2.54mm_Vertical
J28: Sensor 4; PinHeader_1x02_P2.54mm_Vertical
J29: Sensor 5; PinHeader_1x02_P2.54mm_Vertical
J30: Sensor 6; PinHeader_1x02_P2.54mm_Vertical
J31: Sensor 7; PinHeader_1x02_P2.54mm_Vertical
K1: Rele 5V; Relay_SPDT_Finder_36.11
K2: Rele 7V; Relay_SPDT_Finder_36.11
K3: Arranque; Relay_SPDT_Finder_36.11
Q1: IO25; TO-220-3_Vertical
Q2: IO26; TO-220-3_Vertical
Q3: IO27; TO-220-3_Vertical
Q4: IO14; TO-220-3_Vertical
Resistencia1: Resistencia 5V; R_Axial_DIN0204_L3.6mm_D1.6mm_P5.08mm_Horizontal
Resistencia2: Resistencia 7V; R_Axial_DIN0204_L3.6mm_D1.6mm_P5.08mm_Horizontal
Sensor_Corriente1: Sensor_Corriente
Step_5V1, Step_7V1: XL4016
Step_Chino1: Step_Down_Chinp
U1: ESP32-DEVKITC-32D; MODULE_ESP32-DEVKITC-32D; PARTREV V4
U2: RASPBERRY_PI_4B_4GB; MODULE_RASPBERRY_PI_4B_4GB; PARTREV 4

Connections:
3V3: J7.2, Sensor_Corriente1.1 (VCC), U1.J2-1 (3V3)
7V: J1.2, J5.2, J14.2, K2.11
Acelerador: J3.2, U1.J3-11 (IO17)
Corriente: Sensor_Corriente1.2 (OUT), U1.J2-7 (IO32)
L_PWM: Driver_Motor1.5 (LPWM), U1.J3-8 (IO19)
unnamed: D1.2 (A), D2.3 (G), Resistencia1.1
unnamed: D1.1 (K), D2.2 (A), J11.1, K1.14, Step_5V1.3 (Vout)
unnamed: D2.1 (K), K1.A1
unnamed: D3.2 (A), D4.3 (G), Resistencia2.1
unnamed: D3.1 (K), D4.2 (A), J13.1, K2.14, Step_7V1.3 (Vout)
unnamed: D4.1 (K), K2.A1
unnamed: Driver_Motor1.4 (VIN), F1.1, Step_5V1.1 (Vin), Step_Chino1.4 (Vout_-)
unnamed: Driver_Motor1.2 (VIN_MOTOR_1), J25.2
unnamed: Driver_Motor1.1 (VIN_MOTOR_2), J25.1
unnamed: J4.2, U1.J3-15 (IO2)
unnamed: J4.3, U1.J3-14 (IO0)
unnamed: J4.4, U1.J3-13 (IO4)
unnamed: J4.5, U1.J3-12 (IO16)
unnamed: J8.1, Q1.3 (S)
unnamed: J16.1, Q1.2 (D)
unnamed: J17.1, Q2.3 (S)
unnamed: J18.1, Q2.2 (D)
unnamed: J19.1, Q3.3 (S)
unnamed: J20.1, Q3.2 (D)
unnamed: J21.1, Q4.3 (S)
unnamed: J22.1, Q4.2 (D)
unnamed: J23.1, K3.11
unnamed: J24.1, K3.12
unnamed: Sensor_Corriente1.4 (Cable1), Step_7V1.1 (Vin)
unnamed: F1.2, Sensor_Corriente1.5 (Cable2)
unnamed: U2.1 (3V3), U2.17 (3V3)
unnamed: U2.S1 (SHIELD), U2.S2 (SHIELD), U2.S3 (SHIELD), U2.S4 (SHIELD)
RX ESP: U1.J3-5 (RXD0), U2.8 (GPIO14/TXD0)
R_EN_L_EN: Driver_Motor1.7 (L_EN), Driver_Motor1.8 (R_EN), U1.J3-6 (IO21)
R_PWM: Driver_Motor1.6 (RPWM), U1.J3-9 (IO18)
Rele1: Q1.1 (G), U2.26 (GPIO7/~SPI_CE1)
Rele2: Q2.1 (G), U2.24 (GPIO8/~SPI_CE0)
Rele3: Q3.1 (G), U2.22 (GPIO25/GPIO_GEN6)
Rele4: Q4.1 (G), U2.18 (GPIO24/GPIO_GEN5)
Rele5: K3.A2, U2.36 (GPIO16)
Sensor Adelante 1: J10.1, U1.J2-15 (IO13)
Sensor Adelante 2: J10.2, U1.J2-13 (IO12)
Sensor Adelante 3: J10.3, U1.J2-12 (IO14)
Sensor Adelante 4: J10.4, U1.J2-11 (IO27)
Sensor Atras 1: J10.5, U1.J2-10 (IO26)
Sensor Atras 2: J10.6, U1.J2-9 (IO25)
Sensor Atras 3: J10.7, U1.J2-8 (IO33)
SensorGiro: J2.1, U1.J3-16 (IO15)
Servo1: J5.1, U1.J3-3 (IO22)
Servo2: J1.1, U1.J3-2 (IO23)
TRIG: J9.1, J9.2, J9.3, J9.4, J9.5, J9.6, J9.7, U1.J3-10 (IO5)
TX ESP: U1.J3-4 (TXD0), U2.10 (GPIO15/RXD0)

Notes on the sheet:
SISTEMA SEGURIDAD 5V
CONTROL CUATRI
SISTEMA SEGURIDAD 7V

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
